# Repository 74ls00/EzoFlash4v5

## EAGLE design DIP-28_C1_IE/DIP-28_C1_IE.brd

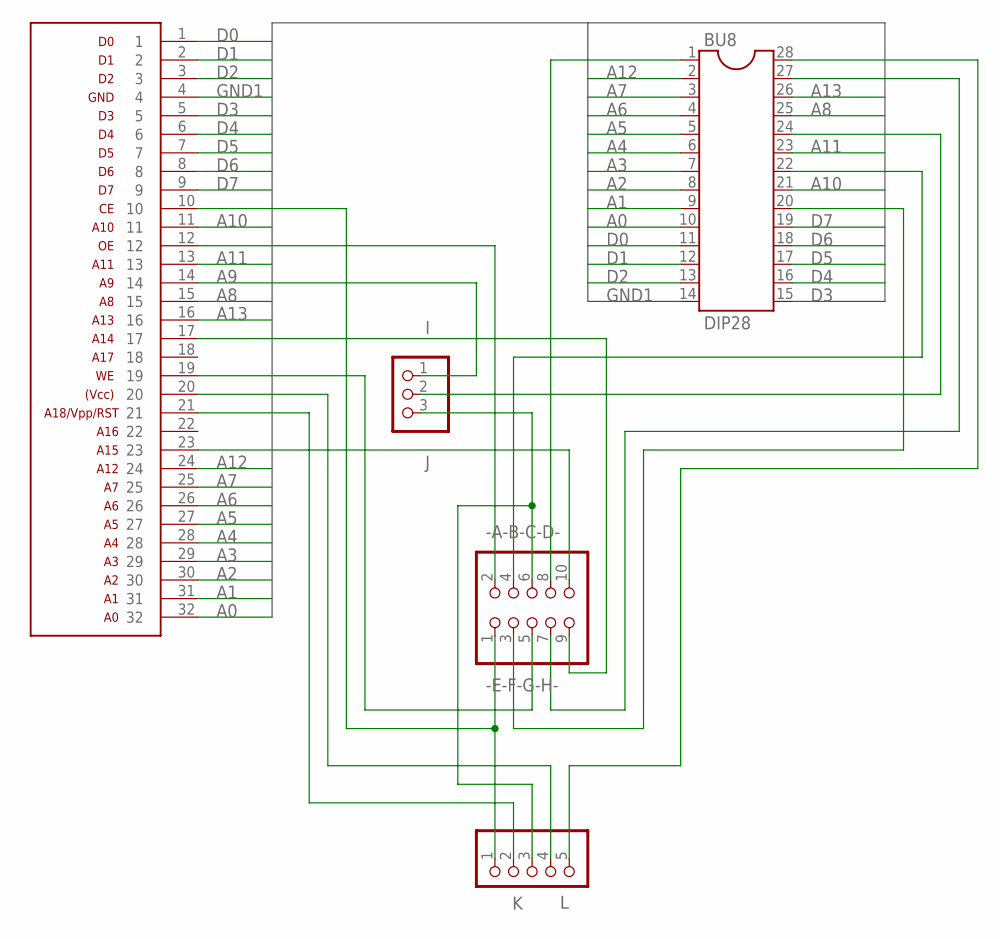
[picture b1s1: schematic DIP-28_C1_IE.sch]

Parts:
-A-B-C-D-: -E-F-G-H-; 2X05
BU6: EZO-BU3
BU8: DIP28; DIP28P
I: J; 1X03
K: L; 1X05

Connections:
A0: BU6.32, BU8.10
A1: BU6.31, BU8.9
A2: BU6.30, BU8.8
A3: BU6.29, BU8.7
A4: BU6.28, BU8.6
A5: BU6.27, BU8.5
A6: BU6.26, BU8.4
A7: BU6.25, BU8.3
A8: BU6.15, BU8.25
A9: BU6.14, I.1
A10: BU6.11, BU8.21
A11: BU6.13, BU8.23
A12: BU6.24, BU8.2
A13: BU6.16, BU8.26
D0: BU6.1, BU8.11
D1: BU6.2, BU8.12
D2: BU6.3, BU8.13
D3: BU6.5, BU8.15
D4: BU6.6, BU8.16
D5: BU6.7, BU8.17
D6: BU6.8, BU8.18
D7: BU6.9, BU8.19
GND1: BU6.4, BU8.14
unnamed: BU8.24, I.2
unnamed: -A-B-C-D-.3, BU8.20
unnamed: -A-B-C-D-.2, BU6.12
unnamed: -A-B-C-D-.4, BU8.22
unnamed: -A-B-C-D-.6, I.3, K.3
unnamed: -A-B-C-D-.8, BU8.1
unnamed: -A-B-C-D-.10, BU6.23
unnamed: -A-B-C-D-.9, BU6.17
unnamed: -A-B-C-D-.7, BU8.27
unnamed: -A-B-C-D-.5, BU6.19
unnamed: -A-B-C-D-.1, BU6.10, K.1
unnamed: BU6.21, K.2
unnamed: BU6.20, K.4
unnamed: BU8.28, K.5

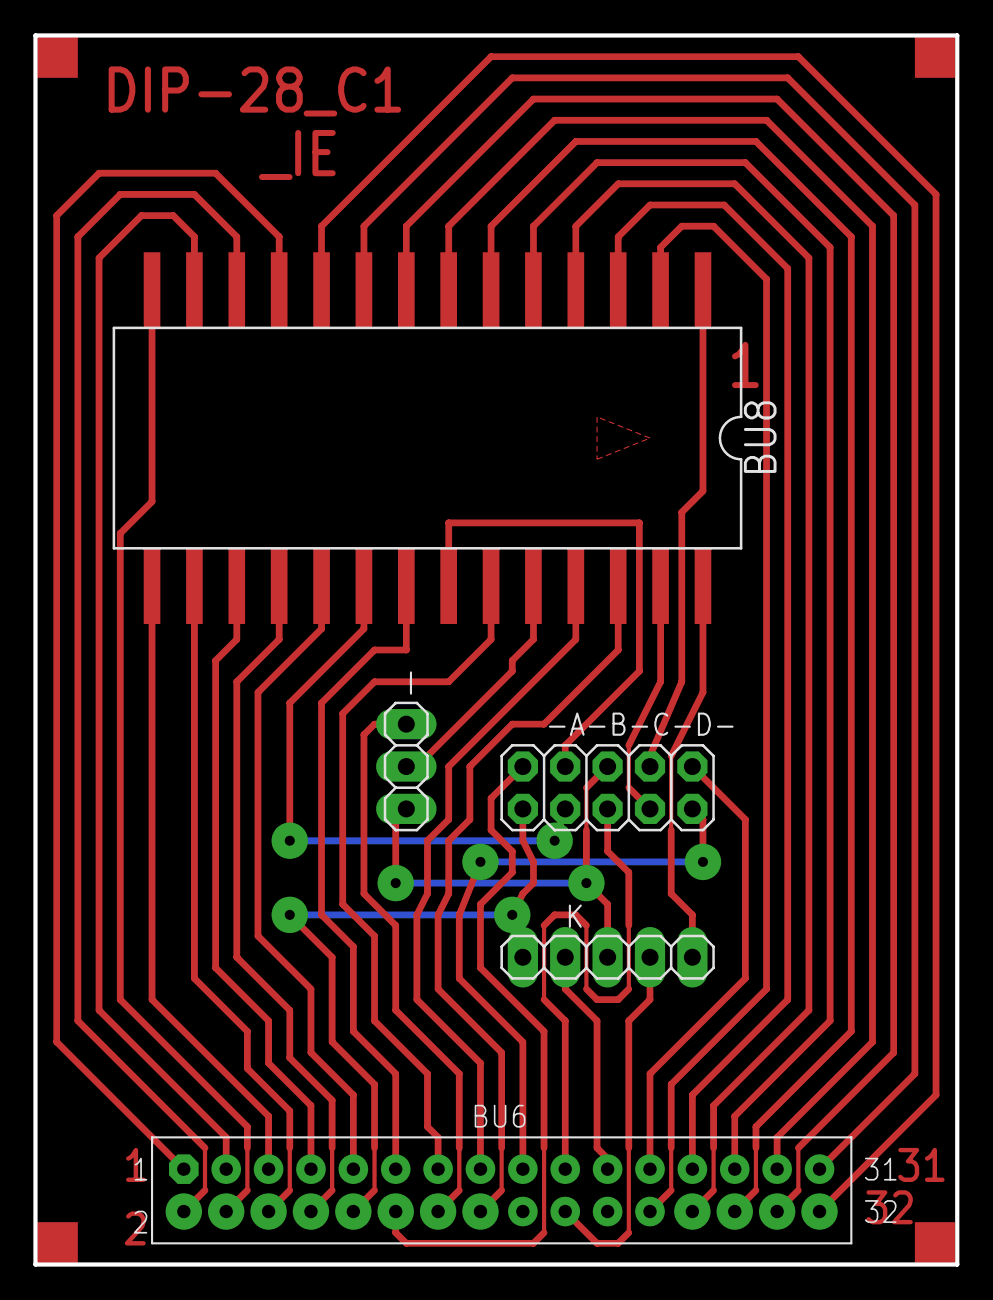
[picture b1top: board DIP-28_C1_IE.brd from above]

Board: 2 copper layers, 55.2 x 73.7 mm, 5 parts (0 on the bottom side), 37 nets.
